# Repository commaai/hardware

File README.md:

# comma hardware

This repo is the home for all comma.ai hardware.

Some of the hardware is fully open source and published here, and the rest is an archive of past hardware sold on the comma shop.

## comma shop

The [comma shop](https://comma.ai/shop) offers our latest hardware for sale.

## Join us!

Want to design and build cool hardware like this?  We're [hiring](https://comma.ai/jobs) hardware engineers and interns; try our [hardware challenge](https://github.com/commaai/harness_tester_challenge).

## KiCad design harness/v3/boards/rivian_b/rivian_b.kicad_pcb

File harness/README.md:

# Car harness

## harness connector

The harness serves as the connection to the car. 
In most cars, it is typically connected to the ADAS camera, with only a few exceptions. 
The wiring diagrams for the harnesses we sell are open-sourced and can be found in [here](./v3).

Does your car model lack support from openpilot, and you’re eager to change that? The journey starts with [creating a custom harness](./BUILD_HARNESS.md)!

## harness box

The harness box is like an adapter between the car harness and the comma 3X. 
An integrated relay ensures that you can remove the c3x without your car giving you an error message.
The relay can be controlled by software and opens automatically when openpilot starts.
Internally, the camera's can bus is separated from the rest of the car. 
Some can messages between the camera and the car are simply passed through by software, but messages such as steering commands from the ADAS camera are intercepted and replaced by openpilot.

**The harness box must be connected to the harness, otherwise your car will display error messages.**

## obd-c

The [OBD-C Cable](https://comma.ai/shop/obd-c-cable) is a USB-C cable where all internal lines are fully connected, complying with the USB-C 3.1 Gen 2 or USB-C 3.2 Gen 2 specifications. 
The OBD-C pinout is specifed [here](./OBD-C.sch.pdf).
You might ask why are there short and long cables in the store? The long cable is typically used when the car harness is not connected at the adas camera near the comma 3X. 

All the exceptions are listed here on this [page]("https://www.comma.ai/shop/car-harness")

**NOTE: bad cables are common source of errors. To avoid unnecessary frustration, we recommend purchasing a [high-quality cable](https://comma.ai/shop/obd-c-cable) that meets the specifications.**

## comma power

comma power is an optional, yet recommended, addition to enhance your device's capabilities. 
The four-pin connection provides both power and OBD CAN connectivity.

While you can operate the device without comma power, it will only be powered while driving.
**With comma power** the device remains continuously powered, unlocking more features like a dashcam, remote tracking, SSH access, and more.

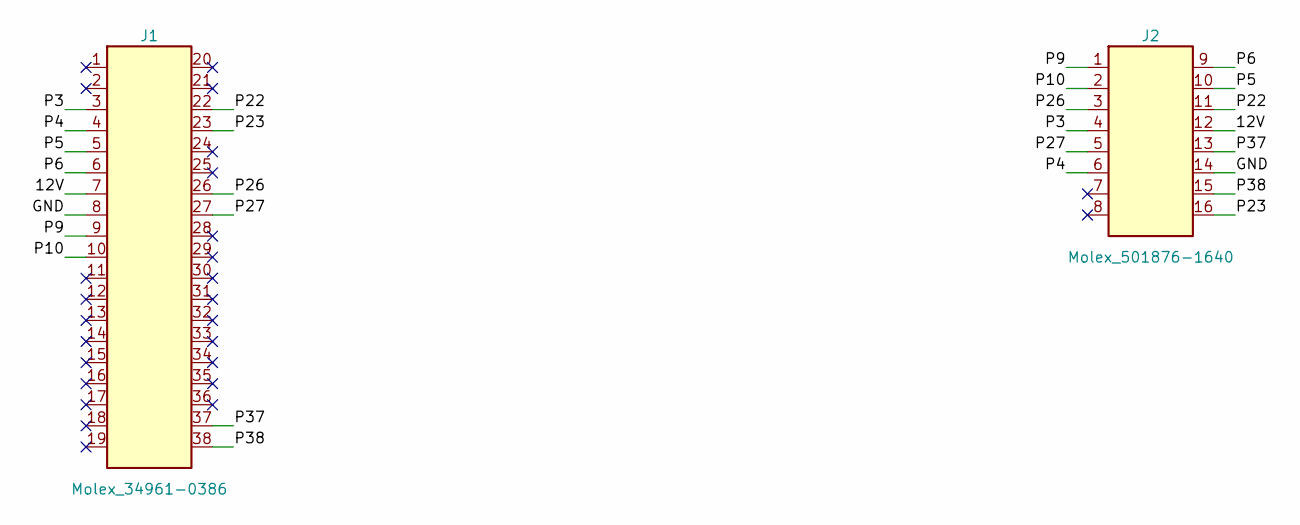
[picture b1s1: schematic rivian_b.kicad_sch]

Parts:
J1: Molex_34961-0386
J2: Molex_501876-1640; Molex_5018761640

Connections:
/12V: J1.7, J2.12
/GND: J1.8, J2.14
/P3: J1.3, J2.4
/P4: J1.4, J2.6
/P5: J1.5, J2.10
/P6: J1.6, J2.9
/P9: J1.9, J2.1
/P10: J1.10, J2.2
/P22: J1.22, J2.11
/P23: J1.23, J2.16
/P26: J1.26, J2.3
/P27: J1.27, J2.5
/P37: J1.37, J2.13
/P38: J1.38, J2.15

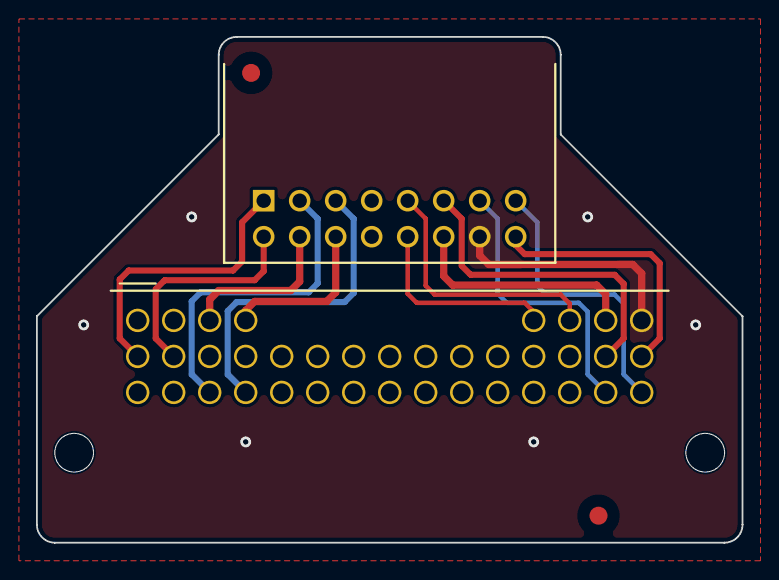
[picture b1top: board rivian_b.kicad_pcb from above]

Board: 2 copper layers, 39.2 x 28.1 mm, 5 parts (1 on the bottom side), 14 nets.

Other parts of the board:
FID1, FID2: Fiducial_1mm_Mask2mm
LOGO1: comma_logo

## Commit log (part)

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2025-02-17 fix image links
2025-02-17 Fix broken image links (#3)
2025-03-07 add power extender
2025-03-07 update harness schematics
2025-03-24 update harness images
2025-04-08 add rivian and tesla A
2025-04-08 update harness images (#5)
2025-05-04 comma zero
2025-05-14 Update README.md (#8)
2025-06-25 Note late c3s have different sensors
    Closes #2
2025-06-25 Apply suggestions from code review
2025-06-25 Note late c3s have different sensors (#9)
    * Note late c3s have different sensors
    Closes #2
    * Apply suggestions from code review
    * Update README.md
    ---------
2025-06-28 comma zero (#7)
    * comma zero
    * Update README.md
    ---------
2025-08-27 comma three flashing instructions
2025-08-29 flash
2025-08-30 feat: add last openpilot version to comma 3
2025-09-01 feat: add last openpilot version to comma 3 (#13)
2025-11-09 add tesla b
2025-11-09 comma four
2025-11-09 fix url
2025-11-10 shop links
2025-11-10 body
2026-01-26 add debug connector pinout
2026-04-10 add c4 hat/stand
2026-04-13 bosch c pcba
2026-04-15 Rename C4_stand.3mf to comma_four_stand.3mf
2026-04-15 body: add comma four hat (#21)
    * add comma 4 hat 3D file for body v1
2026-04-16 Added BYD-f harness from Gutek. BYD bounty that MLP claims
